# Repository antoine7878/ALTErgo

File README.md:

# Custom split keyboard inspired by Redox

## PCB

## Case

## keyboard

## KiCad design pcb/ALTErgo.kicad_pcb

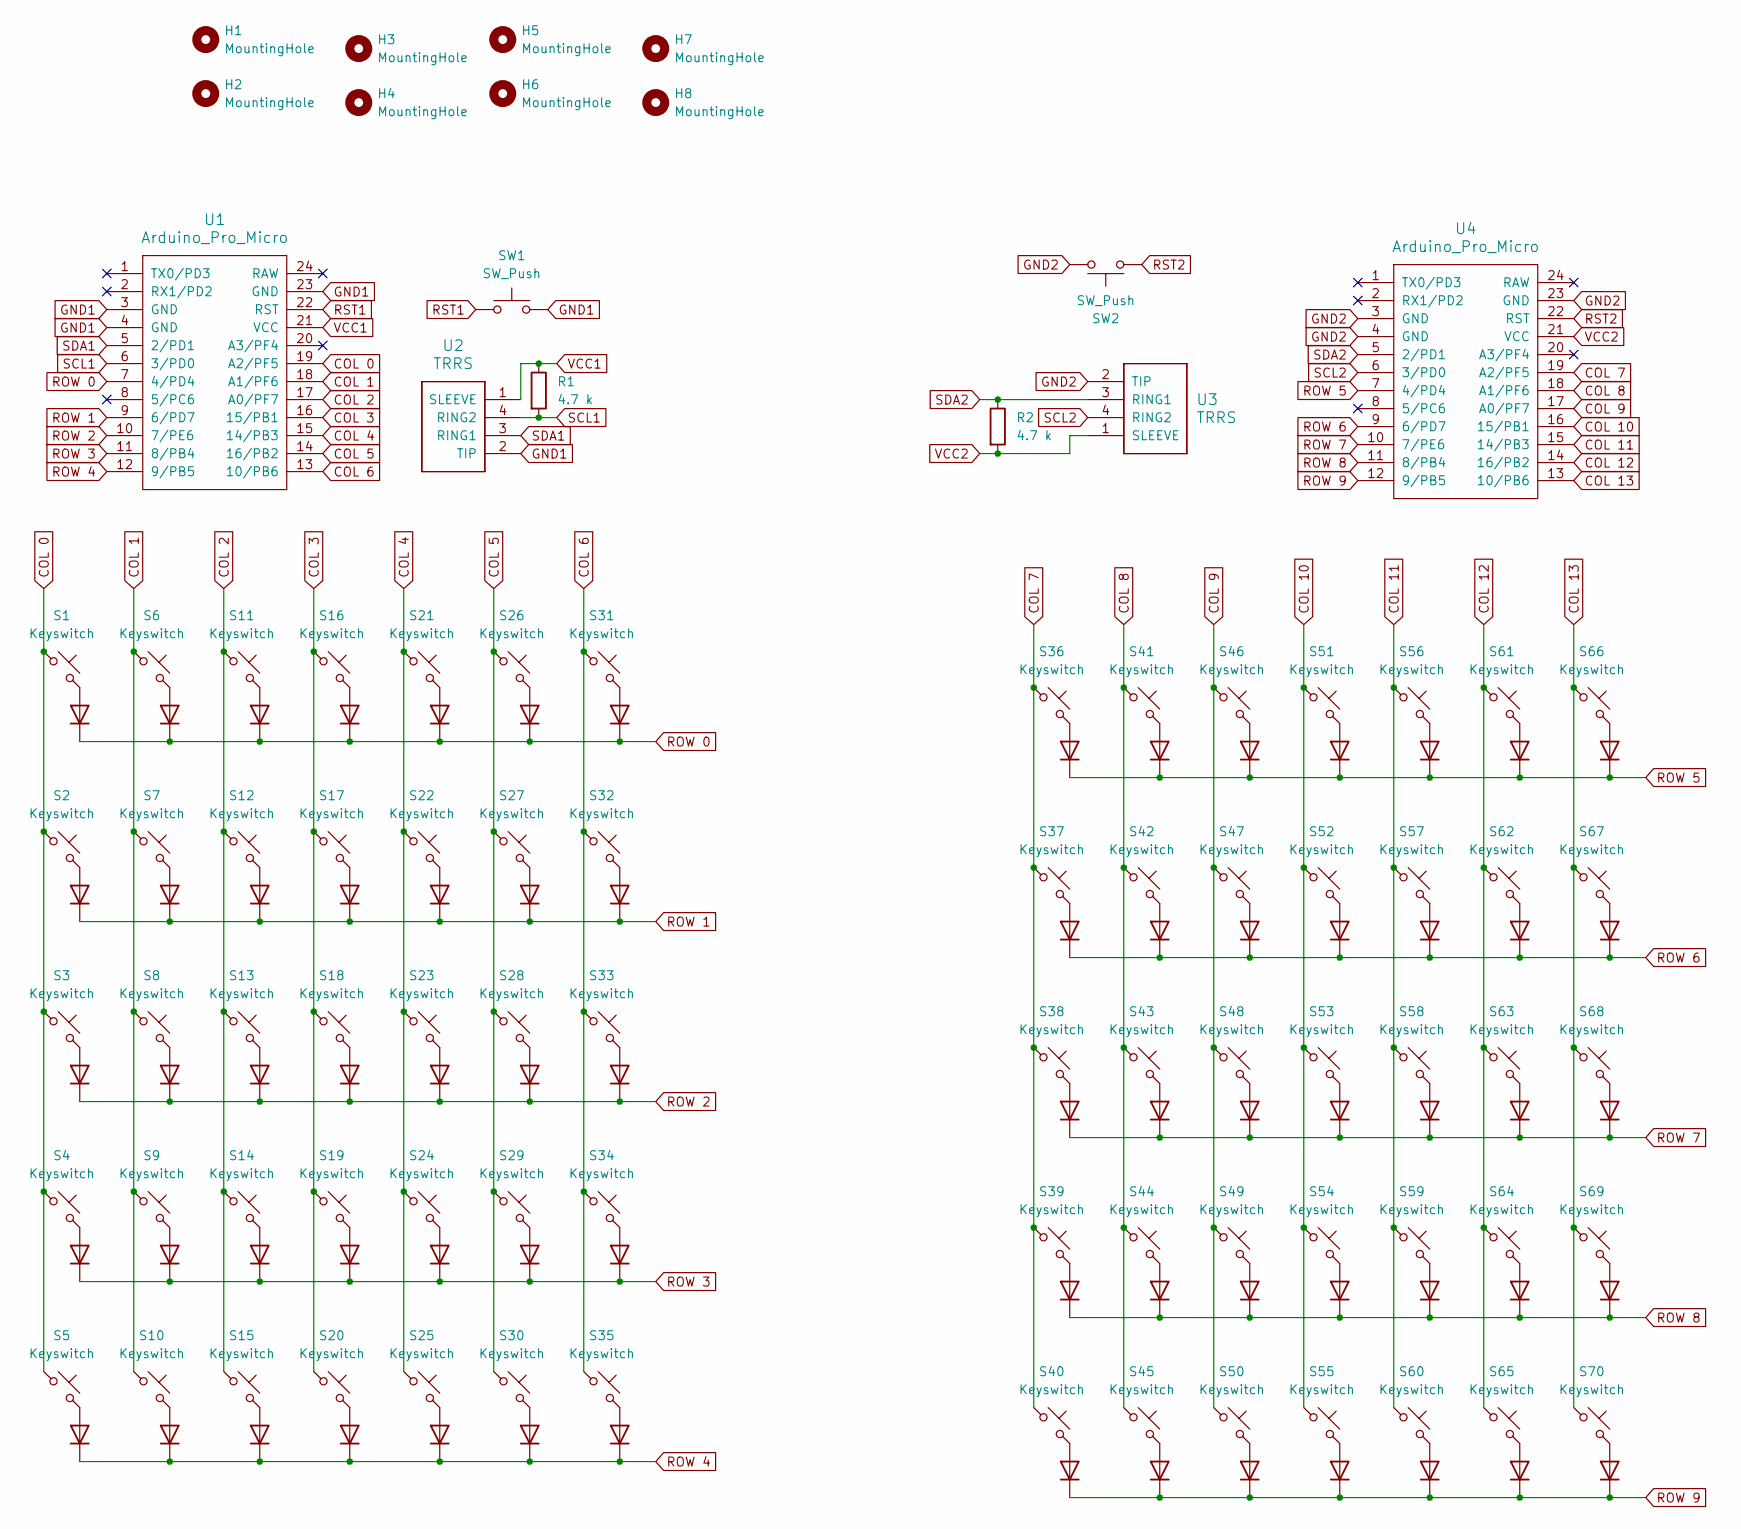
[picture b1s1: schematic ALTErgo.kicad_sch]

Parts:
D1, D2, D3, D4, D5, D6, D7, D8, D9, D10, D11, D12, D13, D14, D15, D16, D17, D18, D19, D20, D21, D22, D23, D24, D25, D26, D27, D28, D29, D30, D31, D32, D33, D34, D35, D36, D37, D38, D39, D40, D41, D42, D43, D44, D45, D46, D47, D48, D49, D50, D51, D52, D53, D54, D55, D56, D57, D58, D59, D60, D61, D62, D63, D64, D65, D66, D67, D68, D69, D70: Diode; Diode_DO-35
H1, H2, H3, H4, H5, H6, H7, H8: MountingHole; MountingHole_4.3mm_M4
R1, R2: 4.7 k; R_Axial_DIN0414_L11.9mm_D4.5mm_P15.24mm_Horizontal
S1, S2, S3, S4, S5, S6, S7, S8, S9, S10, S11, S12, S13, S14, S15, S16, S17, S18, S19, S20, S21, S22, S23, S24, S26, S27, S28, S29, S31, S33, S34, S36, S38, S39, S41, S42, S43, S44, S46, S47, S48, S49, S51, S52, S53, S54, S55, S56, S57, S58, S59, S60, S61, S62, S63, S64, S65, S66, S67, S68, S69, S70: Keyswitch; Hotswap_Choc_V1_1.00u
S25, S50: Keyswitch; Hotswap_Choc_V1_1.25u
S30, S32, S35, S37, S40, S45: Keyswitch; Hotswap_Choc_V1_1.50u
SW1, SW2: SW_Push; SW_Push_1P1T_NO_CK_KMR2
U1, U4: Arduino_Pro_Micro
U2, U3: TRRS; TRRS_PJ-320A

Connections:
COL 0: S1.1, S2.1, S3.1, S4.1, S5.1, U1.19 (A2/PF5)
COL 1: S6.1, S7.1, S8.1, S9.1, S10.1, U1.18 (A1/PF6)
COL 2: S11.1, S12.1, S13.1, S14.1, S15.1, U1.17 (A0/PF7)
COL 3: S16.1, S17.1, S18.1, S19.1, S20.1, U1.16 (15/PB1)
COL 4: S21.1, S22.1, S23.1, S24.1, S25.1, U1.15 (14/PB3)
COL 5: S26.1, S27.1, S28.1, S29.1, S30.1, U1.14 (16/PB2)
COL 6: S31.1, S32.1, S33.1, S34.1, S35.1, U1.13 (10/PB6)
COL 7: S36.1, S37.1, S38.1, S39.1, S40.1, U4.19 (A2/PF5)
COL 8: S41.1, S42.1, S43.1, S44.1, S45.1, U4.18 (A1/PF6)
COL 9: S46.1, S47.1, S48.1, S49.1, S50.1, U4.17 (A0/PF7)
COL 10: S51.1, S52.1, S53.1, S54.1, S55.1, U4.16 (15/PB1)
COL 11: S56.1, S57.1, S58.1, S59.1, S60.1, U4.15 (14/PB3)
COL 12: S61.1, S62.1, S63.1, S64.1, S65.1, U4.14 (16/PB2)
COL 13: S66.1, S67.1, S68.1, S69.1, S70.1, U4.13 (10/PB6)
GND1: SW1.2, U1.3 (GND), U1.4 (GND), U1.23 (GND), U2.2 (TIP)
GND2: SW2.2, U3.2 (TIP), U4.3 (GND), U4.4 (GND), U4.23 (GND)
unnamed: D1.2 (A), S1.2
unnamed: D2.2 (A), S2.2
unnamed: D3.2 (A), S3.2
unnamed: D4.2 (A), S4.2
unnamed: D5.2 (A), S5.2
unnamed: D6.2 (A), S6.2
unnamed: D7.2 (A), S7.2
unnamed: D8.2 (A), S8.2
unnamed: D9.2 (A), S9.2
unnamed: D10.2 (A), S10.2
unnamed: D11.2 (A), S11.2
unnamed: D12.2 (A), S12.2
unnamed: D13.2 (A), S13.2
unnamed: D14.2 (A), S14.2
unnamed: D15.2 (A), S15.2
unnamed: D16.2 (A), S16.2
unnamed: D17.2 (A), S17.2
unnamed: D18.2 (A), S18.2
unnamed: D19.2 (A), S19.2
unnamed: D20.2 (A), S20.2
unnamed: D21.2 (A), S21.2
unnamed: D22.2 (A), S22.2
unnamed: D23.2 (A), S23.2
unnamed: D24.2 (A), S24.2
unnamed: D25.2 (A), S25.2
unnamed: D26.2 (A), S26.2
unnamed: D27.2 (A), S27.2
unnamed: D28.2 (A), S28.2
unnamed: D29.2 (A), S29.2
unnamed: D30.2 (A), S30.2
unnamed: D31.2 (A), S31.2
unnamed: D32.2 (A), S32.2
unnamed: D33.2 (A), S33.2
unnamed: D34.2 (A), S34.2
unnamed: D35.2 (A), S35.2
unnamed: D36.2 (A), S36.2
unnamed: D37.2 (A), S37.2
unnamed: D38.2 (A), S38.2
unnamed: D39.2 (A), S39.2
unnamed: D40.2 (A), S40.2
unnamed: D41.2 (A), S41.2
unnamed: D42.2 (A), S42.2
unnamed: D43.2 (A), S43.2
unnamed: D44.2 (A), S44.2
unnamed: D45.2 (A), S45.2
unnamed: D46.2 (A), S46.2
unnamed: D47.2 (A), S47.2
unnamed: D48.2 (A), S48.2
unnamed: D49.2 (A), S49.2
unnamed: D50.2 (A), S50.2
unnamed: D51.2 (A), S51.2
unnamed: D52.2 (A), S52.2
unnamed: D53.2 (A), S53.2
unnamed: D54.2 (A), S54.2
unnamed: D55.2 (A), S55.2
unnamed: D56.2 (A), S56.2
unnamed: D57.2 (A), S57.2
unnamed: D58.2 (A), S58.2
unnamed: D59.2 (A), S59.2
unnamed: D60.2 (A), S60.2
unnamed: D61.2 (A), S61.2
unnamed: D62.2 (A), S62.2
unnamed: D63.2 (A), S63.2
unnamed: D64.2 (A), S64.2
unnamed: D65.2 (A), S65.2
unnamed: D66.2 (A), S66.2
unnamed: D67.2 (A), S67.2
unnamed: D68.2 (A), S68.2
unnamed: D69.2 (A), S69.2
unnamed: D70.2 (A), S70.2
ROW 0: D1.1 (K), D6.1 (K), D11.1 (K), D16.1 (K), D21.1 (K), D26.1 (K), D31.1 (K), U1.7 (4/PD4)
ROW 1: D2.1 (K), D7.1 (K), D12.1 (K), D17.1 (K), D22.1 (K), D27.1 (K), D32.1 (K), U1.9 (6/PD7)
ROW 2: D3.1 (K), D8.1 (K), D13.1 (K), D18.1 (K), D23.1 (K), D28.1 (K), D33.1 (K), U1.10 (7/PE6)
ROW 3: D4.1 (K), D9.1 (K), D14.1 (K), D19.1 (K), D24.1 (K), D29.1 (K), D34.1 (K), U1.11 (8/PB4)
ROW 4: D5.1 (K), D10.1 (K), D15.1 (K), D20.1 (K), D25.1 (K), D30.1 (K), D35.1 (K), U1.12 (9/PB5)
ROW 5: D36.1 (K), D41.1 (K), D46.1 (K), D51.1 (K), D56.1 (K), D61.1 (K), D66.1 (K), U4.7 (4/PD4)
ROW 6: D37.1 (K), D42.1 (K), D47.1 (K), D52.1 (K), D57.1 (K), D62.1 (K), D67.1 (K), U4.9 (6/PD7)
ROW 7: D38.1 (K), D43.1 (K), D48.1 (K), D53.1 (K), D58.1 (K), D63.1 (K), D68.1 (K), U4.10 (7/PE6)
ROW 8: D39.1 (K), D44.1 (K), D49.1 (K), D54.1 (K), D59.1 (K), D64.1 (K), D69.1 (K), U4.11 (8/PB4)
ROW 9: D40.1 (K), D45.1 (K), D50.1 (K), D55.1 (K), D60.1 (K), D65.1 (K), D70.1 (K), U4.12 (9/PB5)
RST1: SW1.1, U1.22 (RST)
RST2: SW2.1, U4.22 (RST)
SCL1: R1.2, U1.6 (3/PD0), U2.4 (RING2)
SCL2: U3.4 (RING2), U4.6 (3/PD0)
SDA1: U1.5 (2/PD1), U2.3 (RING1)
SDA2: R2.1, U3.3 (RING1), U4.5 (2/PD1)
VCC1: R1.1, U1.21 (VCC), U2.1 (SLEEVE)
VCC2: R2.2, U3.1 (SLEEVE), U4.21 (VCC)

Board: 2 copper layers, 156 parts (72 on the bottom side), 104 nets, no tracks yet.

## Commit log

2024-01-04 first
2024-01-04 readme
2024-01-04 read
2026-01-07 First
    readme
    read
    add README.md
